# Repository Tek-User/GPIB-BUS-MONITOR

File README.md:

# GPIB-BUS-MONITOR

This is an Arduino project.  The program uses two GPIB bus monitoring strategies to watch traffic on the bus.  It can be a Sniffer where it is as close to invisible to the bus as possible.  Or it can be a Listener which actively participates on the bus for listening purposes.  The Arduino platform with minimal hardware as a "listener" can support only a few other devices on the bus because it has current limits on pulling-down the bus when asserting a signal.

Both strategies were tested with two other devices on the bus:  a National Instruments GPIB controller card and a Tektronix 2440 DSO oscilloscope and both techniques functioned well.

The hardware used is an Arduino Nano.  It has enough IO to manage all 16 GPIB signals.

Included in this project is an EAGLE PCB design to connect the Nano to a GPIB header.  You can use a Centronics style GPIB connector or simply hand solder all the GPIB wires directly to the PCB.

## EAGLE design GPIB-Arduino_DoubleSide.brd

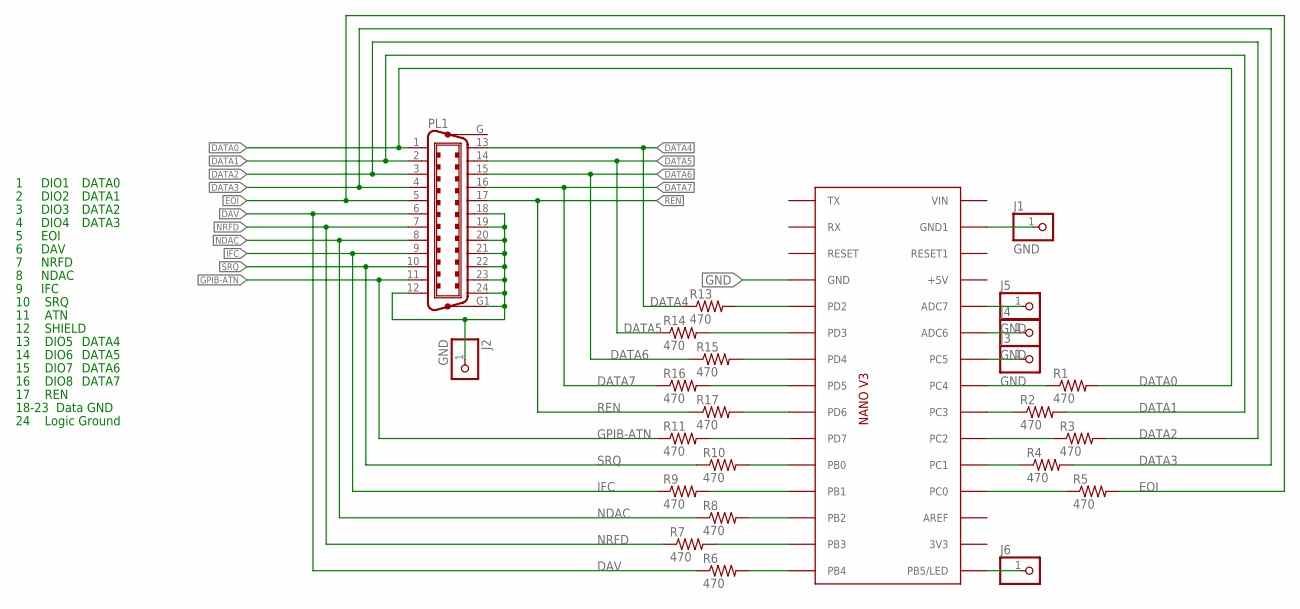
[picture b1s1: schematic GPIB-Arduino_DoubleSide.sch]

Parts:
J1, J2, J3, J4, J5: GND; 1X01_ROUND
J6: PINHD1X01ROUND; 1X01_ROUND
PL1: C24HP; 24HP
R1, R2, R3, R4, R5, R6, R7, R8, R9, R10, R11, R13, R14, R15, R16, R17: 470; R-1/8W
U$6: ARDUINONANO; PDIP-32

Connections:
DATA0: PL1.1, R1.2
DATA1: PL1.2, R2.2
DATA2: PL1.3, R3.2
DATA3: PL1.4, R4.2
DATA4: PL1.13, R13.1
DATA5: PL1.14, R14.1
DATA6: PL1.15, R15.1
DATA7: PL1.16, R16.1
DAV: PL1.6, R6.1
EOI: PL1.5, R5.2
GND: J1.1, J2.1, PL1.12, PL1.18, PL1.19, PL1.20, PL1.21, PL1.22, PL1.23, PL1.24, PL1.G1, U$6.GND, U$6.GND1
GPIB-ATN: PL1.11, R11.1
IFC: PL1.9, R9.1
unnamed: R1.1, U$6.A3 (PC4)
unnamed: R2.1, U$6.A4 (PC3)
unnamed: R3.1, U$6.A5 (PC2)
unnamed: R4.1, U$6.A6 (PC1)
unnamed: R5.1, U$6.A7 (PC0)
unnamed: R11.2, U$6.D7
unnamed: R10.2, U$6.D8 (PB0)
unnamed: R9.2, U$6.D9 (PB1)
unnamed: R8.2, U$6.D10 (PB2)
unnamed: R7.2, U$6.D11 (PB3)
unnamed: R6.2, U$6.D12 (PB4)
unnamed: J5.1, U$6.A0 (ADC7)
unnamed: R13.2, U$6.D2
unnamed: R14.2, U$6.D3
unnamed: R15.2, U$6.D4
unnamed: R16.2, U$6.D5
unnamed: R17.2, U$6.D6
unnamed: J4.1, U$6.A1 (ADC6)
unnamed: J3.1, U$6.A2 (PC5)
unnamed: J6.1, U$6.D13 (PB5/LED)
NDAC: PL1.8, R8.1
NRFD: PL1.7, R7.1
REN: PL1.17, R17.1
SRQ: PL1.10, R10.1

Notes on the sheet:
1 DIO1
2 DIO2
3 DIO3
4 DIO4
5 EOI
6 DAV
7 NRFD
8 NDAC
9 IFC
10 SRQ
11 ATN
12 SHIELD
13 DIO5
14 DIO6
15 DIO7
16 DIO8
17 REN
18-23 Data GND
24 Logic Ground
DATA0
DATA1
DATA2
DATA3
DATA4
DATA5
DATA6
DATA7

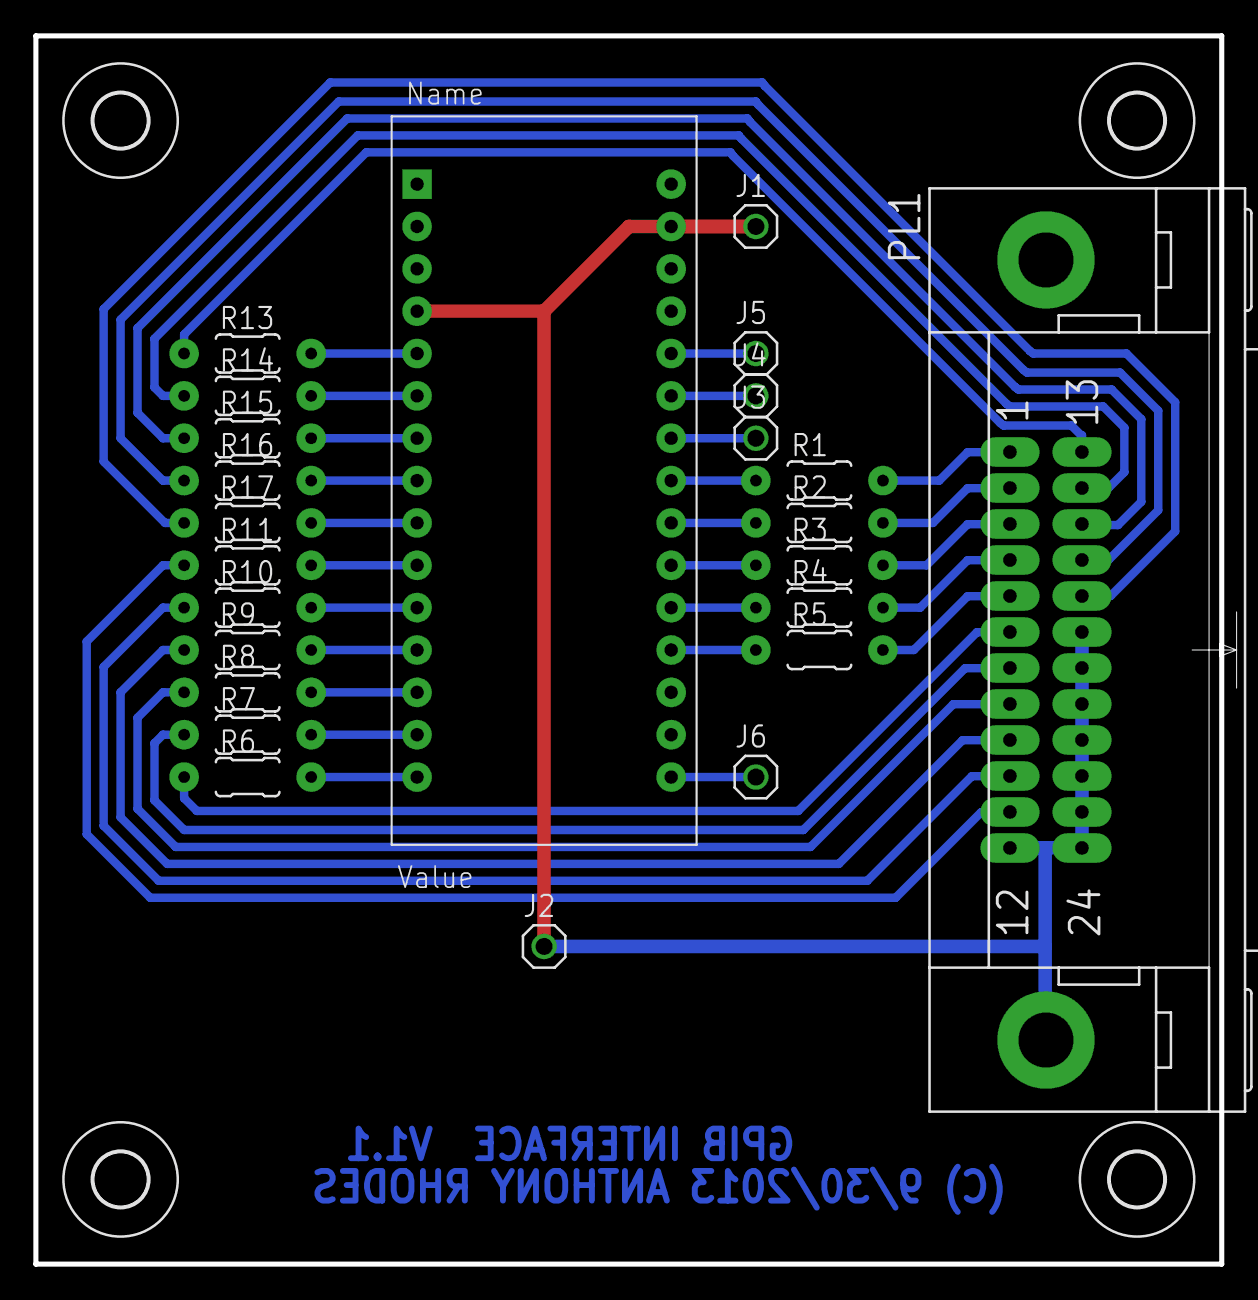
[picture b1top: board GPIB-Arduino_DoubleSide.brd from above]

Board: 2 copper layers, 71.1 x 73.7 mm, 28 parts (0 on the bottom side), 37 nets.

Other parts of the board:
U$1, U$2, U$3, U$5: 3,2

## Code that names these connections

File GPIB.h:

#ifndef GPIB_h
#define GPIB_h

#include <inttypes.h>
#include <stdint.h>
#include <stdbool.h>

// PIN DEFINITIONS
#define _HIGH    1
#define _LOW     0
#define _ASSERTED  0
#define _RELEASED  1

//0=C4    4=C2
//1=c1    5=C1
//2=C    6=D3
//3=D4    7=D5

#if defined (ARDUINO_AVR_UNO) || defined (ARDUINO_AVR_NANO)
#warning "UNO or Nano"
    //#Define DATA0 C.4
    #define DATA0_PORT PORTC
    #define DATA0_PIN PINC
    #define DATA0_DDR DDRC
    #define DATA0_BIT _BV(4)

    //#Define DATA1 C.3
    #define DATA1_PORT PORTC
    #define DATA1_PIN PINC
    #define DATA1_DDR DDRC
    #define DATA1_BIT _BV(3)

    //#Define DATA2 C.2
    #define DATA2_PORT PORTC
    #define DATA2_PIN PINC
    #define DATA2_DDR DDRC
    #define DATA2_BIT _BV(2)

    //#Define DATA3 C.1
    #define DATA3_PORT PORTC
    #define DATA3_PIN PINC
    #define DATA3_DDR DDRC
    #define DATA3_BIT _BV(1)

    //#Define DATA4 D.2
    #define DATA4_PORT PORTD
    #define DATA4_PIN PIND
    #define DATA4_DDR DDRD
    #define DATA4_BIT _BV(2)

    //#Define DATA5 D.3
    #define DATA5_PORT PORTD
    #define DATA5_PIN PIND
    #define DATA5_DDR DDRD
    #define DATA5_BIT _BV(3)

    //#Define DATA6 D.4
    #define DATA6_PORT PORTD
    #define DATA6_PIN PIND
    #define DATA6_DDR DDRD
    #define DATA6_BIT _BV(4)

    //#Define DATA7 D.5
    #define DATA7_PORT PORTD
    #define DATA7_PIN PIND
    #define DATA7_DDR DDRD
    #define DATA7_BIT _BV(5)
    
    //#Define REN   D.6
    #define REN_PORT PORTD
    #define REN_PIN PIND
    #define REN_DDR DDRD
    #define REN_BIT _BV(6)
    
    //#Define ATN   D.7
    #define ATN_PORT PORTD
    #define ATN_PIN PIND
    #define ATN_DDR DDRD
     #define ATN_BIT _BV(7)

    //#Define SRQ   B.0
    #define SRQ_PORT PORTB
    #define SRQ_PIN PINB
    #define SRQ_DDR DDRB
    #define SRQ_BIT _BV(0)
  
    //#Define IFC   B.1
    #define IFC_PORT PORTB
    #define IFC_PIN PINB
    #define IFC_DDR DDRB
    #define IFC_BIT _BV(1)

    //#Define NDAC  B.2
    #define NDAC_PORT PORTB
    #define NDAC_PIN PINB
    #define NDAC_DDR DDRB
    #define NDAC_BIT _BV(2)

    //#Define NRFD  B.3
    #define NRFD_PORT PORTB
    #define NRFD_PIN PINB
    #define NRFD_DDR DDRB
    #define NRFD_BIT _BV(3)

    //#Define DAV   B.4
    #define DAV_PORT PORTB
    #define DAV_PIN PINB
    #define DAV_DDR DDRB
    #define DAV_BIT _BV(4)

    //#Define EOI   C.0
    #define EOI_PORT PORTC
    #define EOI_PIN PINC
    #define EOI_DDR DDRC
    #define EOI_BIT _BV(0)

    //#Define LED   B.5
    #define LED_PORT PORTB
    #define LED_PIN PINB
    #define LED_DDR DDRB
    #define LED_BIT _BV(5)

    //#Define FREE  C.5
    #define CS_PIN 10   //using the SD shield, it uses pin 10 for the card select.


#elif defined(ARDUINO_AVR_MEGA) || defined(ARDUINO_AVR_MEGA2560)  
     //#Define DATA0 A.0
    #define DATA0_PORT PORTA
    #define DATA0_PIN PINA
    #define DATA0_DDR DDRA
    #define DATA0_BIT _BV(0)

    //#Define DATA1 A.2
    #define DATA1_PORT PORTA
    #define DATA1_PIN PINA
    #define DATA1_DDR DDRA
    #define DATA1_BIT _BV(2)

    //#Define DATA2 A.4
    #define DATA2_PORT PORTA
    #define DATA2_PIN PINA
    #define DATA2_DDR DDRA
    #define DATA2_BIT _BV(4)

    //#Define DATA3 A.6
    #define DATA3_PORT PORTA
    #define DATA3_PIN PINA
    #define DATA3_DDR DDRA
    #define DATA3_BIT _BV(6)

    //#Define DATA4 A.1
    #define DATA4_PORT PORTA
    #define DATA4_PIN PINA
    #define DATA4_DDR DDRA
    #define DATA4_BIT _BV(1)

    //#Define DATA5 A.3
    #define DATA5_PORT PORTA
    #define DATA5_PIN PINA
    #define DATA5_DDR DDRA
    #define DATA5_BIT _BV(3)

    //#Define DATA6 A.5
    #define DATA6_PORT PORTA
    #define DATA6_PIN PINA
    #define DATA6_DDR DDRA
    #define DATA6_BIT _BV(5)

    //#Define DATA7 A.7
    #define DATA7_PORT PORTA
    #define DATA7_PIN PINA
    #define DATA7_DDR DDRA
    #define DATA7_BIT _BV(7)

    //#Define REN   C.6
    #define REN_PORT PORTC
    #define REN_PIN PINC
    #define REN_DDR DDRC
    #define REN_BIT _BV(6)
    
    //#Define ATN   C.1
    #define ATN_PORT PORTC
    #define ATN_PIN PINC
    #define ATN_DDR DDRC
     #define ATN_BIT _BV(1)

    //#Define SRQ   C.0
    #define SRQ_PORT PORTC
    #define SRQ_PIN PINC
    #define SRQ_DDR DDRC
    #define SRQ_BIT _BV(0)
  
    //#Define IFC   C.3
    #define IFC_PORT PORTC
    #define IFC_PIN PINC
    #define IFC_DDR DDRC
    #define IFC_BIT _BV(3)

    //#Define NDAC  C.2
    #define NDAC_PORT PORTC
    #define NDAC_PIN PINC
    #define NDAC_DDR DDRC
    #define NDAC_BIT _BV(2)

    //#Define NRFD  C.5
    #define NRFD_PORT PORTC
    #define NRFD_PIN PINC
    #define NRFD_DDR DDRC
    #define NRFD_BIT _BV(5)

    //#Define DAV   C.4
    #define DAV_PORT PORTC
    #define DAV_PIN PINC
    #define DAV_DDR DDRC
    #define DAV_BIT _BV(4)

    //#Define EOI   C.7
    #define EOI_PORT PORTC
    #define EOI_PIN PINC
    #define EOI_DDR DDRC
    #define EOI_BIT _BV(7)

    //#Define LED   B.7
    #define LED_PORT PORTB
    #define LED_PIN PINB
    #define LED_DDR DDRB
    #define LED_BIT _BV(7)

    //Define SwitchSense  L.4
    #define SENSE_PORT PORTL
    #define SENSE_PIN PINL
    #define SENSE_DDR DDRL
    #define SENSE_BIT _BV(4)

    //Define SwitchPoll1  L.3
    #define SPOLL1_PORT PORTL
    #define SPOLL1_PIN PINL
    #define SPOLL1_DDR DDRL
    #define SPOLL1_BIT _BV(3)

    //Define SwitchPoll2  L.2
    #define SPOLL2_PORT PORTL
    #define SPOLL2_PIN PINL
    #define SPOLL2_DDR DDRL
    #define SPOLL2_BIT _BV(2)

    //Define SwitchPoll3  L.1
    #define SPOLL3_PORT PORTL
    #define SPOLL3_PIN PINL
    #define SPOLL3_DDR DDRL
    #define SPOLL3_BIT _BV(1)

    //Define SwitchPoll4  L.0
    #define SPOLL4_PORT PORTL
    #define SPOLL4_PIN PINL
    #define SPOLL4_DDR DDRL
    #define SPOLL4_BIT _BV(0)

    //SD card defines
    #define CS_PIN  53    //using the standard SPI pins on the Mega double row header, card select is pin 53
    //#define CS_PIN  10
    //#define MOSI_PIN  51  //PIN_SPI_MOSI
    //#define MISO_PIN 50   //PIN_SPI_MISO predefined value
    //#define SCK_PIN 52    //SCK_PIN is predefined!



#else
    #error "NO CPU DEFINED!!"
#endif



//#define DMASK 0x3C  //'0011-1100  'data high nibble shifted right 2
//#define CMASK 0x1e  //'0001-1110  'data low nibble shifted left 1





// SPECIAL CHARACTERS
#define _CR    13
#define _LF    10
#define _ESC   27
#define _PLUS  43


#define ClientADDR 1  //GPIB address of the clinet
#define UNL 0x3F //=63d
#define UNT 0x5F 
#define TADDR 64
#define LADDR 32


//GLOBAL DATA
//uint8_t receiveState = 0;     //for state machine of receive GPIB data
//bool receivingData  = false;   //indicates GPIB receive is in progress




//Dim CFlip as ByteVectorData ({
//  &H00, &H08, &H04, &H0C
//  &H02, &H0A, &H06, &H0E
//  &H01, &H09, &H05, &H0D
//  &H03, &H0B, &H07, &H0F
//})

//This will look up the reverse bits in a nibble
//uint8_t bitReverse[] ={0x00, 0x08, 0x04, 0x0C, 0x02, 0x0A, 0x06, 0x0E, 0x01, 0x09, 0x05, 0x0D, 0x03, 0x0B, 0x07, 0x0F};






// PUBLIC USER INTERFACE FUNCTIONS
void        GPIBInit(void);
void        GPIBInitSniff(void);
uint16_t    GPIBWriteData(char* data, uint16_t count, bool useEOI);
uint16_t    GPIBWriteString (char* data, bool useEOI);
void        GPIBWriteCmd(char* data, uint16_t _length, bool useEOI);
void        GPIBInitListen(void);
void        GPIBInitTalk();
void        GPIBInterfaceClear(void);
uint8_t     GPIBDataReady(void);
uint16_t    GPIBGetData(char* buffer, uint16_t len, uint16_t timeOut = 10000);
void        GPIBMonitor(void);
void        GPIBSendState(void);

//  PRIVATE FUNCTIONS
void    GPIBRelease(volatile uint8_t *gpibPORT, volatile uint8_t *gpibDDR, uint8_t gpibBIT);
void    GPIBAssert(volatile uint8_t *gpibPORT, volatile uint8_t *gpibDDR, uint8_t gpibBIT);
void    GPIBClear(volatile uint8_t *gpibPORT, volatile uint8_t *gpibDDR, uint8_t gpibBIT);
void    GPIBFloat(volatile uint8_t *gpibPORT, volatile uint8_t *gpibDDR, uint8_t gpibBIT);
void    GPIBClearData(void);
int     GPIBCheck(void);


void    GPIBRemoteEnable(bool state);

uint8_t WaitForDAV(uint8_t state, uint16_t timeLimit);
uint8_t WaitForNRFD(uint8_t state, uint16_t timeLimit);
uint8_t WaitForNDAC(uint8_t state, uint16_t timeLimit);

uint8_t GPIBReadByte(void);
void    _WriteByte(uint8_t data);
uint8_t GPIBWriteByte(uint8_t datum, bool useEOI);


#endif

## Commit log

2019-05-18 Add files via upload
    EAGLE PCB files
